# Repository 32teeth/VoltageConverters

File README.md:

# A Collection of Voltage Converters
> See List Below

Herein are a collection of Voltage / Boost Converters built for different projects using different ICs
Best thing to do is read the whitepapers if you decide to make your own

| Name                              | Gerber                          | Production |
| ----------------------------------------------- | ---------------------------------------------- | ----------------------------------------------- |
| TPS61032-AAA |  |  |
| MCP1642b |  |  |
| MP9361 |  |  |
| TPS61032 |  |  |
| TPS61099x |  |  |
| TPS613222A |  |  |

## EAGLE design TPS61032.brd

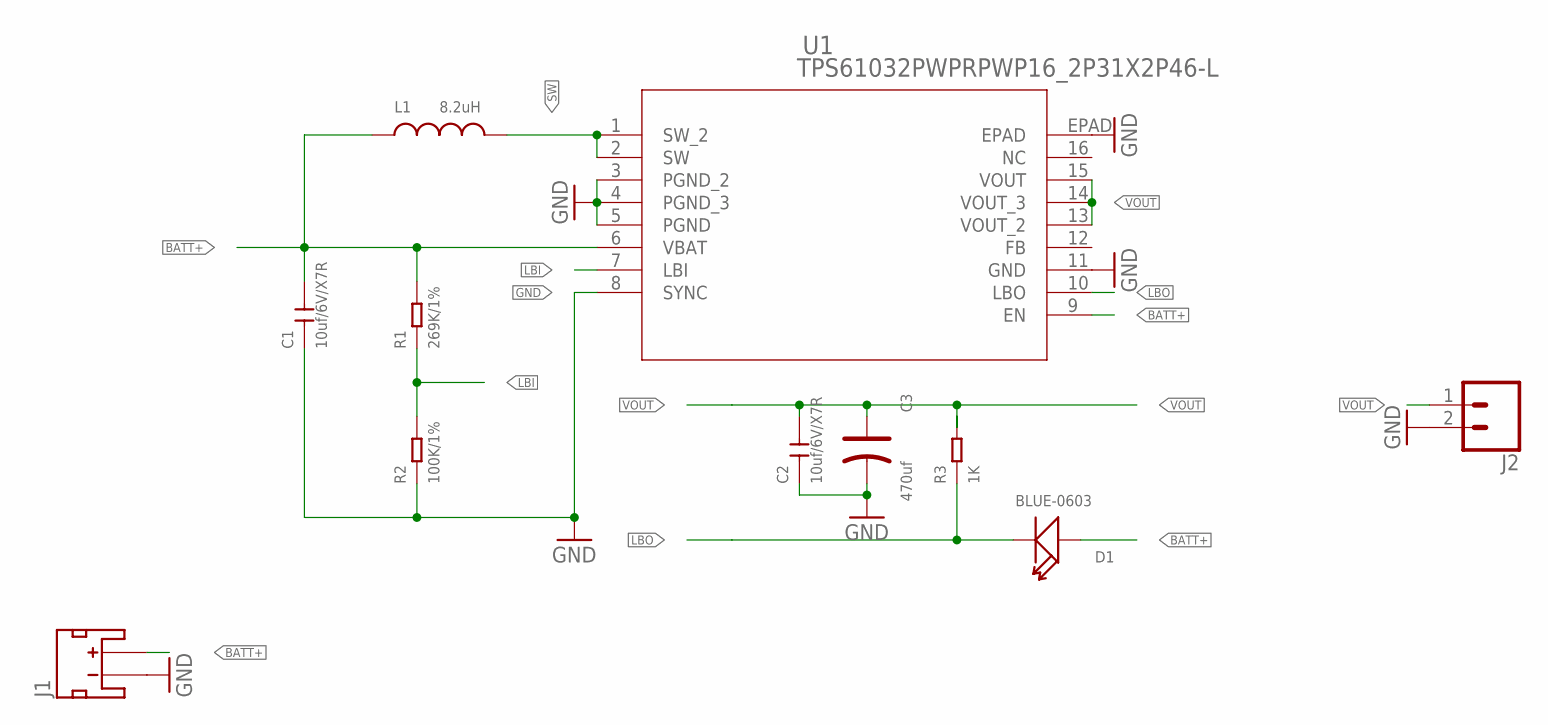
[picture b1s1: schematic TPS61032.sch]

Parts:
C1, C2: 10uf/6V/X7R; C0805
C3: 470uf; AVX-D
D1: BLUE-0603; LED-0603
J1: JST_2MM_MALE; JST-2-SMD
J2: CONN_02PTH4; 1X02_XTRA_BIG
L1: 8.2uH; 7443550820
R1: 269K/1%; R0805
R2: 100K/1%; R0805
R3: 1K; R0603
U1: TPS61032PWPRPWP16_2P31X2P46-L; PWP16_2P31X2P46-L

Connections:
BATT+: C1.2, D1.+, J1.2 (+), L1.1, R1.2, U1.6 (VBAT), U1.9 (EN)
GND: C1.1, C2.1, C3.-, J1.1 (-), J2.2, R2.1, U1.3 (PGND_2), U1.4 (PGND_3), U1.5 (PGND), U1.8 (SYNC), U1.11 (GND), U1.EPAD
LBI: R1.1, R2.2, U1.7 (LBI)
LBO: D1.-, R3.1, U1.10 (LBO)
SW: L1.2, U1.1 (SW_2), U1.2 (SW)
VOUT: C2.2, C3.+, J2.1, R3.2, U1.13 (VOUT_2), U1.14 (VOUT_3), U1.15 (VOUT)

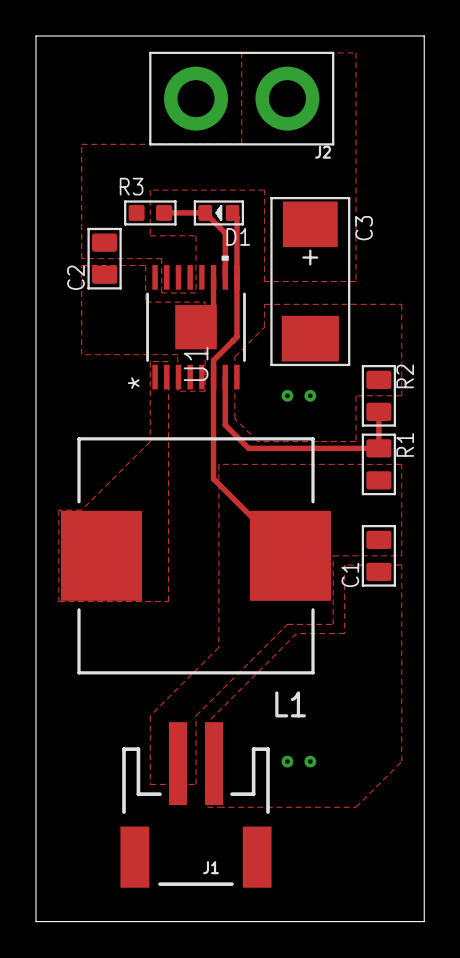
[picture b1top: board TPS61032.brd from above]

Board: 2 copper layers, 21.6 x 49.2 mm, 11 parts (0 on the bottom side), 6 nets.

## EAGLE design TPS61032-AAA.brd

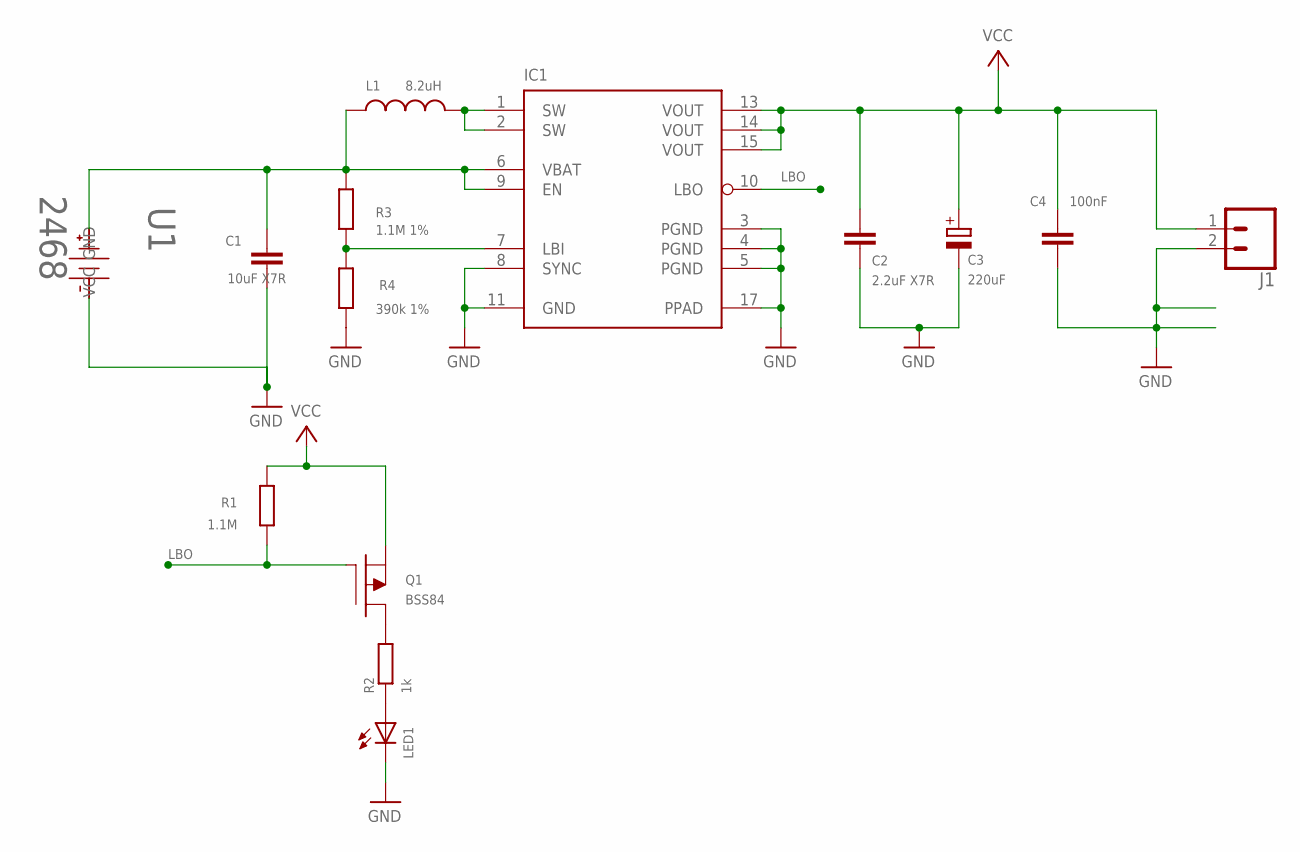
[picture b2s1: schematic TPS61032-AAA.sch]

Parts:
C1: 10uF X7R; CAPC2012X130N
C2: 2.2uF X7R; CAPC2012X130N
C3: 220uF; CAPMP3528X210N
C4: 100nF; CAPC1608X55N
IC1: TPS61032; MO-153+PAD
J1: CONN_02PTH4; 1X02_XTRA_BIG
L1: 8.2uH; 7443550820
LED1: LED0603; LEDC1608X60N
Q1: BSS84; SOT95P240X110-3N
R1: 1.1M; RESC1508X63N
R2: 1k; RESC1508X63N
R3: 1.1M 1%; RESC1508X63N
R4: 390k 1%; RESC1508X63N
U1: 2468; BAT_HLDR_2468

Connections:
GND: C1.2, C2.2, C3.2 (-), C4.2, IC1.3 (PGND), IC1.4 (PGND), IC1.5 (PGND), IC1.8 (SYNC), IC1.11 (GND), IC1.17 (PPAD), J1.2, LED1.1 (C), R4.1, U1.GND
LBI: IC1.7 (LBI), R3.1, R4.2
LBO: IC1.10 (LBO), Q1.1 (GATE), R1.1
LED: LED1.2 (A), R2.1
LOW: Q1.3 (DRAIN), R2.2
SW: IC1.1 (SW), IC1.2 (SW), L1.2
VBAT: C1.1, IC1.6 (VBAT), IC1.9 (EN), L1.1, R3.2, U1.VCC
VCC: C2.1, C3.1 (+), C4.1, IC1.13 (VOUT), IC1.14 (VOUT), IC1.15 (VOUT), J1.1, Q1.2 (SOURCE), R1.2

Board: 2 copper layers, 14 parts (1 on the bottom side), 8 nets, no tracks yet.

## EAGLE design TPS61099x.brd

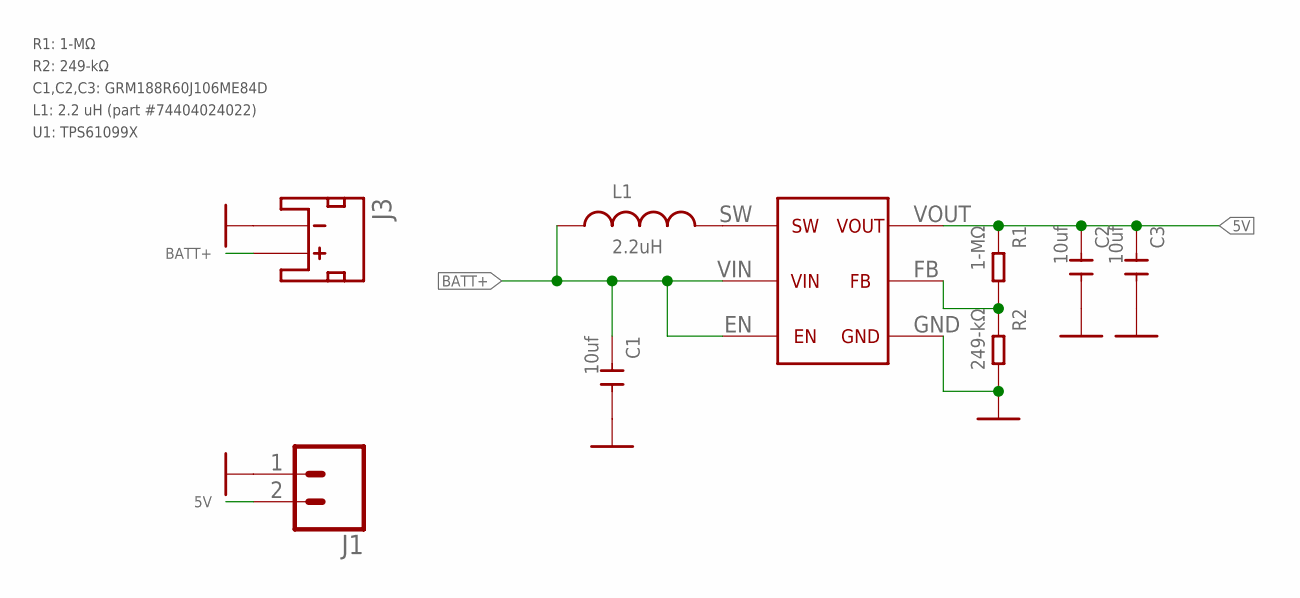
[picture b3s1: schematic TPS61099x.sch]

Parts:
C1, C2, C3: 10uf; C0805
J1: CONN_02PTH4; 1X02_XTRA_BIG
J3: Batt Conn; JST-2-SMD
L1: 2.2uH; WE-LQS_2512
R1: 1-MΩ; R0805
R2: 249-kΩ; R0805
U$1: TPS61099X

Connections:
5V: C2.1, C3.1, J1.2, R1.1, U$1.VOUT
BATT+: C1.1, J3.2 (+), L1.1, U$1.EN, U$1.VIN
GND: C1.2, C2.2, C3.2, J1.1, J3.1 (-), R2.2, U$1.GND
unnamed: L1.2, U$1.SW
unnamed: R1.2, R2.1, U$1.FB

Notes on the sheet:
R1: 1-MΩ R2: 249-kΩ C1,C2,C3: GRM188R60J106ME84D L1: 2.2 uH (part #74404024022) U1: TPS61099X

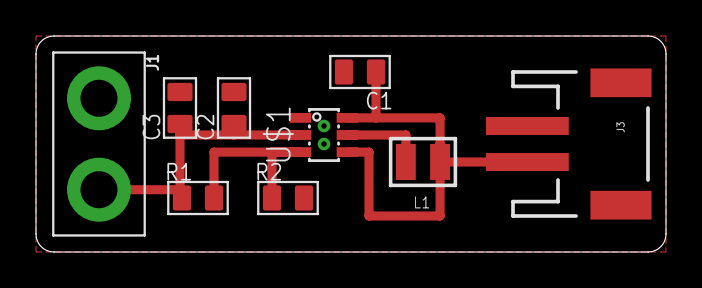
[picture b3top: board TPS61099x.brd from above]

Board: 2 copper layers, 35.0 x 12.0 mm, 9 parts (0 on the bottom side), 5 nets.

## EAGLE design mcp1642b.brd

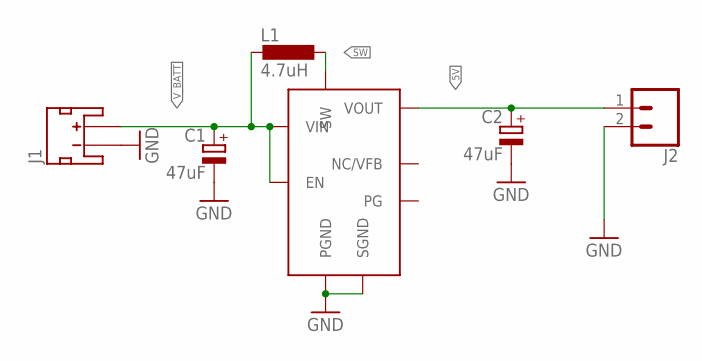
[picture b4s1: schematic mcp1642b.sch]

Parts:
C1, C2: 47uF; 153CLV-0505
J1: JST_2MM_MALE; JST-2-SMD
J2: CONN_02PTH4; 1X02_XTRA_BIG
L1: 4.7uH; POWER-CHOKE_WE-TPC
U11: MCP1642B

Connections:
5V: C2.+, J2.1, U11.VOUT
GND: C1.-, C2.-, J1.1 (-), J2.2, U11.PGND, U11.SGND
SW: L1.1, U11.SW
V_BATT: C1.+, J1.2 (+), L1.2, U11.EN, U11.VIN

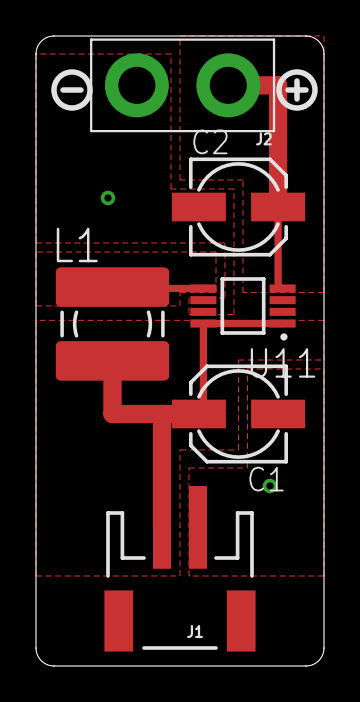
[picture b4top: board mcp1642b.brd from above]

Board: 2 copper layers, 16.0 x 35.0 mm, 6 parts (0 on the bottom side), 4 nets.

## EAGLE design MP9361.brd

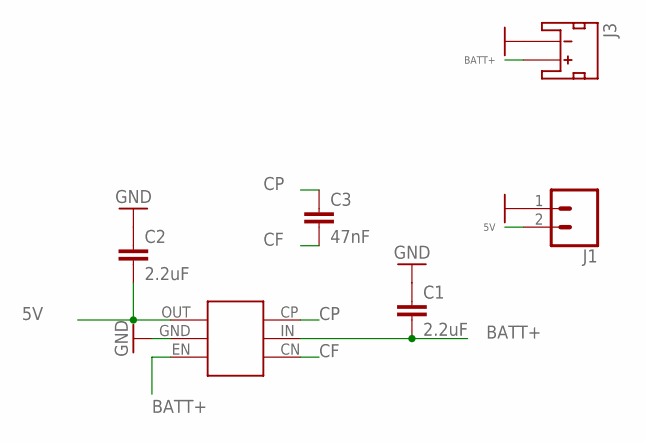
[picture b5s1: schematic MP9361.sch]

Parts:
C1, C2: 2.2uF; 0805
C3: 47nF; 0603
J1: CONN_02PTH4; 1X02_XTRA_BIG
J3: Batt Conn; JST-2-SMD
U1: MP9361

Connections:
5V: C2.2, J1.2, U1.OUT
BATT+: C1.2, J3.2 (+), U1.EN, U1.IN
CF: C3.2, U1.CN
CP: C3.1, U1.CP
GND: C1.1, C2.1, J1.1, J3.1 (-), U1.GND

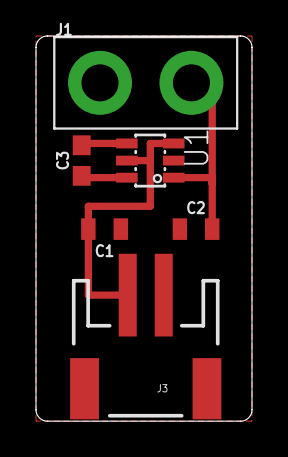
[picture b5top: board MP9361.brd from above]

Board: 2 copper layers, 12.0 x 21.4 mm, 6 parts (0 on the bottom side), 5 nets.

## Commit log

2019-01-18 Fri 18 Jan 2019 11:23:44 EST - initial commit from forked private repo
2019-01-29 Mon 28 Jan 2019 22:16:21 EST - updated MCP1642 device with planes
2019-01-29 Mon 28 Jan 2019 22:17:14 EST - updated MCP1642 device with planes
2019-01-29 Tue 29 Jan 2019 06:33:06 EST
2019-01-29 Tue 29 Jan 2019 07:05:45 EST
2019-03-06 Wed 6 Mar 2019 10:52:50 EST - added AAA alkaline version of TPS61032
2019-03-06 Wed 6 Mar 2019 10:53:50 EST - name change
2019-05-17 Fri 17 May 2019 16:01:28 EDT - added README.md
2019-05-18 Fri 17 May 2019 23:10:17 EDT - added README.md
2019-05-21 Tue 21 May 2019 11:01:09 EDT - Production Images Added, Repo made Public
2019-05-21 Tue 21 May 2019 11:01:44 EDT - Production Images Added, Repo made Public

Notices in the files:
parts and their libraries:
SparkFun-Capacitors: Licensing: Creative Commons ShareAlike 4.0 International - https://creativecommons.org/licenses/by-sa/4.0
PowerMagnetics: Copyright: Würth Elektronik
